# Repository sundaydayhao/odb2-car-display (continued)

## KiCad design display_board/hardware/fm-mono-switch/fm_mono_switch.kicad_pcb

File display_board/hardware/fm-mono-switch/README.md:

# RDA5807M + TS5A22364 单声道 FM / 环境传感小板 · A8

直接集成 **RDA5807M 裸芯片**、32.768 kHz 晶振、电源和天线接口。FM 与 ES8311（MP3 / 小智）经 TS5A22364 切换，共用 ESP32-P4 Function EV Board **v1.4** 的 NS4150B 功放和原喇叭。FM 左右声道经电阻合成单声道。

**状态：首板原型设计完成，已布线。KiCad 10.0.5 原生 ERC、DRC、原理图与 PCB 一致性均为零问题；106 个物理引脚的网络与设计意图一致。尚未做实物验证，不是量产验证版本。本次没有修改固件。**

A8新增 **DHT20 温湿度传感器（卧式、感应面朝上）** 和 **VEML7700-TT 光照传感器**，每套各1颗。板子加长至 **40×58mm**，原安装孔位置保留。新增J5两根线接开发板GPIO7/8；详细引脚、装配尺寸、外壳与固件接入见 [SENSORS.md](SENSORS.md)。

D1沿用A7的 **安世 PESD5V0F1BL,315 / C45961**。U3 **ME6211C30M5G-N**、Y1 **Y6OEL89CGI-STUYLC-32.768K** 和FM/音频部分的元件、焊盘、既有走线保持不变。

A6引入的音频方案继续使用 **TI TS5A22364DGSR / C105181，VSSOP-10 外露引脚**，0.5mm节距、3×3mm本体。TI标为ACTIVE；2026-09-24公开LCSC页面记录库存4719颗、1颗起购/步进，100颗报价阶梯USD0.4479/颗。库存未锁定，国内人民币价和即时交付以新配单为准。相较最早讨论的TS5A22362，本型号当次现货更多、价格更低；两者电气功能有差异，不能直接按同系列替换。A6重接U1的4/5/7/8脚，并将R5/R6改成1kΩ串联限流；必须使用A6或A7 PCB，不能在A5原板上直接换芯片。RDA5807M、GPIO及R83/R84外部接法不变。

## 文件

- `fm_mono_switch.kicad_pro`：打开工程；同名 `.kicad_sch` / `.kicad_pcb` 为完整原理图和已布线 PCB。
- `output/pdf/wiring.pdf`：三页中文接线和安装图，含 R83/R84 官方丝印位置及卧式传感器安装图。
- `output/pdf/schematic.pdf`：完整原理图，可放大查看。
- `output/board-3d.png`、`output/wiring.png`、`output/assembly.png`、`output/sensors.png`：预览；DHT20模型为简化机械包络。
- `PROCUREMENT.md`：逐项降本、原立创报价错配与交期说明。
- `BOM-LCSC-A8.csv`：只列每套用量，1套=1块小板；导入立创时把“每套用量”映射为数量，按实际需求填写采购套数。排针不装，损耗另加。
- `BOM-cost.csv`：每套用量、每套净用料参考金额、MOQ和来源。沿用已核对的阶梯单价，不代表购买1套时的成交价；重新配单确认。
- `BOM.csv`：分组工程物料表，明确列出“每套用量”；`output/fabrication/`：Gerber、钻孔和贴装坐标。
- `VERIFICATION.md`、`output/verification.json`：检查范围和文件校验值。
- `Mono.kicad_sym`、`Mono.pretty`、`libs/`：本地符号和历史库；U1为TI VSSOP-10，U2为MSOP-10，使用核对过的KiCad标准MSOP-10封装及模型。
- `reference/RDA5807M.pdf`：用户提供的裸芯片手册副本；其他依据见 `SOURCES.md`。

## 外部接线：4 根音频线 + 5 根电源 / 控制线 + 2 根传感器线

断电，**拆下开发板 R83、R84 两颗 0Ω 电阻**。保留 C39、C40、C58、C59、R146、R147。用万用表的导通档确认焊盘所属支路，再焊接细软线；不要按照片的左右方向猜测。

| 小板接口 | 开发板焊点 | 导通识别依据 |
|---|---|---|
| J1.1 / CP | R83 的 ES8311 侧焊盘 | 通向 C39 的 R83 侧焊盘 |
| J1.2 / CN | R84 的 ES8311 侧焊盘 | 通向 C40 的 R84 侧焊盘 |
| J2.1 / AP | R83 的功放侧焊盘 | 通向 C59 的 R83 侧焊盘 |
| J2.2 / AN | R84 的功放侧焊盘 | 通向 C58 的 R84 侧焊盘 |
| J4.1 / 3V3 | 开发板 J1.17 | 3.3 V 电源 |
| J4.2 / GND | 开发板 J1.20 | 共地 |
| J4.3 / SEL | 开发板 J1.15 | GPIO6，音源选择 |
| J4.4 / SDA | 开发板 J1.21 | GPIO2，FM I²C 数据 |
| J4.5 / SCL | 开发板 J1.19 | GPIO3，FM I²C 时钟 |
| J5.1 / SDA7 | 开发板 J1.3 | GPIO7，传感器 I²C 数据 |
| J5.2 / SCL8 | 开发板 J1.5 | GPIO8，传感器 I²C 时钟 |

小板 J1 是两针音频输入，**不是开发板的 J1 排针**。小板接口方形焊盘为 1 脚，J4 顶视图从标有 `3V3` 的方形焊盘依次为 `3V3 / G / SEL / SDA / SCL`。排针可不装，直接焊线。

小板 J3.1 `ANT` 接外置 FM 线天线，可先用约 70–80 cm 导线试验并根据安装环境调整；J3.2 `GND` 为地 / 同轴屏蔽连接。该输入没有车载有源天线的幻象供电。天线尽量远离屏幕排线、USB、DC/DC 和扬声器开关输出。

扬声器仍接开发板 **J16**。FM 接入的是功放之前的小信号通路；不要接到 J16 的 SPK+ / SPK−。四根音频飞线尽量短，CP/CN、AP/AN 分别成对布置，并固定线材以免拉脱焊盘。

## 工作原理与关键器件

| 部分 | 设计 |
|---|---|
| FM 接收 | U2 RDA5807M，MSOP-10，3.0 V 供电 |
| 时钟 | Y1 32.768 kHz 晶振接 RCLK 与 GND；按芯片参考电路使用内部振荡电路 |
| FM 电源 | U3 ME6211C30M5G-N；3.3 V → 3.0 V → FB1 → FM_VDD，C9/C10 就近去耦 |
| 射频输入 | J3 ANT → C6 100 pF → FMIN；D1 PESD5V0F1BL,315 低电容双向 ESD 管 |
| 合成单声道 | L/R 各串 1 µF 隔直及 10 kΩ，再汇合；不直接短接左右输出 |
| 音源切换 | U1 TS5A22364DGSR，两个 SPDT 同时切换功放正负两根输入 |
| 上电默认 | SEL 100 kΩ 下拉，GPIO6=0 接 ES8311，GPIO6=1 接 FM |
| 原功放 | 继续使用 NS4150B；小板上不增设功放 |

RDA5807M **裸芯片引脚**：1 GND、2 FMIN、3 GND、4 SCLK、5 SDIO、6 RCLK、7 VDD、8 GND、9 ROUT、10 LOUT。`fm-module` 目录中 RRD-102 成品模块的焊盘号不同，不能套用。截图出现的 `33.768 kHz` 是笔误，本板为 **32.768 kHz**。

TS5A22364 引脚：1 VCC；2 NO1=FM_MONO；3 COM1=AP；4 NC1=CODEC_P_SW；5 IN1=SEL；6 GND；7 IN2=SEL；8 NC2=CODEC_N_SW；9 COM2=AN；10 NO2=FM_REF。J1的CP/CN分别经R5/R6=1kΩ到NC1/NC2；FM_REF经R4=4.3kΩ接地。R7/R8=100kΩ为功放输入和被选中的音源提供直流参考。

TS5A22364由3.3V经R11=10Ω和C4/C5去耦供电。选通通路范围为VCC−5.5V至VCC，标称3.3V时约−2.2V至+3.3V；3.0V供电测试条件下Ron典型0.61Ω、全温最大0.97Ω，不能把典型值当作全条件保证。逻辑VIH≥1.4V、VIL≤0.6V，与GPIO兼容。未选通NC/NO会通过内部约25Ω放电，TI建议电流不超过±10mA；R5/R6改为1kΩ/1%，若输入瞬时绝对值≤3.6V，仅按最小990Ω计算电流≤3.64mA，FM通路由R1/R2各10kΩ限流。所有音源均经电容隔直，不能引入负直流。此限流计算不代替上电瞬态实测；软件继续停止未使用音源并执行功放静音切换。

I²C 经 R12/R13=100 Ω 串联，R14/R15=4.7 kΩ 拉到 FM_VDD（约 3.0 V）。ESP32 引脚使用开漏 I²C，关闭不需要的内部上拉；小板与主板一起供电。

## PCB 与装配

40 × 58 mm，双层，建议板厚 1.6 mm、1 oz 铜。两个 Ø2.2 mm 非金属化安装孔中心为板左上角起算 (3,3) 和 (37,33) mm，保留原固定点。板上阻容以 0603 为主，接口为 2.54 mm 排针。最小设计线宽 0.15 mm、间距 0.127 mm；普通过孔 0.6 / 0.3 mm。双面地平面已填充，DHT20本体下方两面禁止铺铜，以减小导热；信号细线允许通过。

- U4 DHT20按丝印轮廓**卧放、感应孔朝上**。四脚保持原顺序后弯折入孔，方焊盘为1脚VDD。外壳12.6×16.1×5.8mm，预留约0.5mm离板间隙，装配后本体顶面约6.3mm高；建议外壳局部留至少8mm净空再做首件核对。此高度不包括选装直插排针。
- DHT20在贴片工序后手焊，夹持引脚成形，不能在塑封根部硬折。不要用胶、泡棉或三防漆覆盖感应孔；外壳对应位置开通风孔。弯脚尺寸由首件实物确认。
- U5指定VEML7700-**TT顶视型**，不要换-TR侧视型。外壳开独立透光窗，避免显示屏漏光；装入最终外壳后校准透光衰减。温湿度区避免直晒与热源。

- **U1 TS5A22364DGSR 为 VSSOP-10 / DGS**，两侧外露引脚，3×3mm本体、0.5mm间距。使用已核对包络的KiCad标准MSOP-10焊盘（库命名不同，机械尺寸相容）；不买DRC/VSON或YZP/DSBGA封装。
- U2 是 MSOP-10、0.5 mm 间距；封装三角和模型圆点标明 1 脚。
- Y1 为扬兴 `Y6OEL89CGI-STUYLC-32.768K`（C19272781），目录参数 CL=12.5pF、ESR≤50kΩ、−40～85°C，DT-26 圆柱约 Ø2×6mm。引脚成形至1.9mm孔距。精确承认书与起振裕量仍需首板确认，不能用立创旧报价匹配的 SMD3215 晶体直接替换。
- D1 为安世 **PESD5V0F1BL,315**（C45961），双向、VRWM=5.5V，结电容典型0.4pF/最大0.55pF（1MHz、0V、25°C），SOD882 / DFN1006-2。推荐焊盘0.4×0.7mm、中心距0.7mm与现板一致；整机ESD效果未测试。
- U3 改用带 `-N` 的微盟3.0V稳压器；C7/C8 改4.7µF/10V/X5R，需核对偏压后的有效容量≥1µF并测启动、纹波；不要改用高压差 AMS1117。
- 工程 BOM 已补齐具体品牌、MPN 和商品编号。原用户报价单中的 RDA5807M 仍需订货7–10个工作日，100颗货源及封装须锁单前确认。候选 CPL/BOM 仍需贴片厂核对旋转和料号，不能直接视为下单审核完成。
- 接地 SMD 焊盘采用实连铺铜，装配时需充分预热。Y1、排针可在贴片后手工焊接。

## 软件模式切换

| 模式 | GPIO6 | 音频来源 |
|---|---|---|
| MP3 | 0 | ESP32 解码 → I²S → ES8311 |
| 小智 | 0 | ESP32 语音 → I²S → ES8311 |
| FM | 1 | RDA5807M → 无源合声 → 原功放 |

MP3 和小智共用 ES8311，二者的互斥由软件音频管理负责。进入 FM 时停止 / 静音 ES8311 播放；切换前静音或关闭原 PA，设置 GPIO6，待节点稳定再打开 PA 并淡入。原 PA 控制为 **GPIO53**，不需要增加飞线。FM 模式也需要软件使能这个功放。

现有 FM 驱动使用 GPIO2/3、100 kHz I²C、7 位顺序访问地址 0x10。固件应选择 32.768 kHz 参考时钟，按需要使用强制单声道和 FM 自身音量控制；切换静音延时以首板波形和听感调整。**硬件接线完成不等于现有固件已经实现 GPIO6 与 PA 的联动。**

## 首板检查

1. 焊接后先检查 U1/U2 引脚短路和芯片方向；未连接开发板音频焊盘时，单独检查电源与地是否短路。
2. 输入 3.3 V，确认 FM_VDD 约 3.0 V、U1 电源接近 3.3 V；确认 GPIO6 默认低电平。
3. 验证 I²C 通信、芯片初始化和搜台。普通高电容探头可能使手表晶振停振，优先由芯片工作状态判断或使用合适的低电容探头。
4. 接回 R83/R84 四根飞线，以低音量分别验证 MP3、小智、FM。确认 FM 模式仍打开原功放；测试切换有无明显爆音。
5. 在屏幕刷新、Wi-Fi 传输、USB 供电以及最终安装位置下验证底噪和 FM 接收，按需要调整天线与线束。

## 维护

脚本位于仓库 `tools/fm_mono_switch/`。A8使用交付的原生CAD文件维护；`generate.py`是历史A7生成器，已阻止覆盖A8。`add_sensors_a8.py`为一次性的A7到A8迁移，`route_sensors_a8.py`只为该迁移导入传感器布线。`route.py` / `finish_routes.py`是已拦截的历史A2流程。`finalize.py`整理料号，`verify_final.py`比对网表，`verify_a8_change.py`核对A7元件及全部既有走线保留，`draw_wiring_a2.py`生成当前三页接线图，`package_release.py`导出文件包。

只更新BOM时运行 `python tools/fm_mono_switch/export_bom.py`，不改写原理图和PCB。以后导出的工程表、采购表和成本表只列“每套用量”，不预乘采购套数。`procurement.json` 的 `price_reference_boards` 仅记录历史价格评估基准。

打开工程建议使用KiCad 10。U1/U2均用官方 `Package_SO:MSOP-10_3x3mm_P0.5mm`；U1符号和完整厂商手册已随工程提供。标准焊盘1.50×0.35mm、行中心距4.20mm，按厂商3×3mm本体、4.75–5.05mm引脚总宽复核；焊盘比推荐图的1.02×0.31mm更长，不冒称完全照搬推荐焊盘。

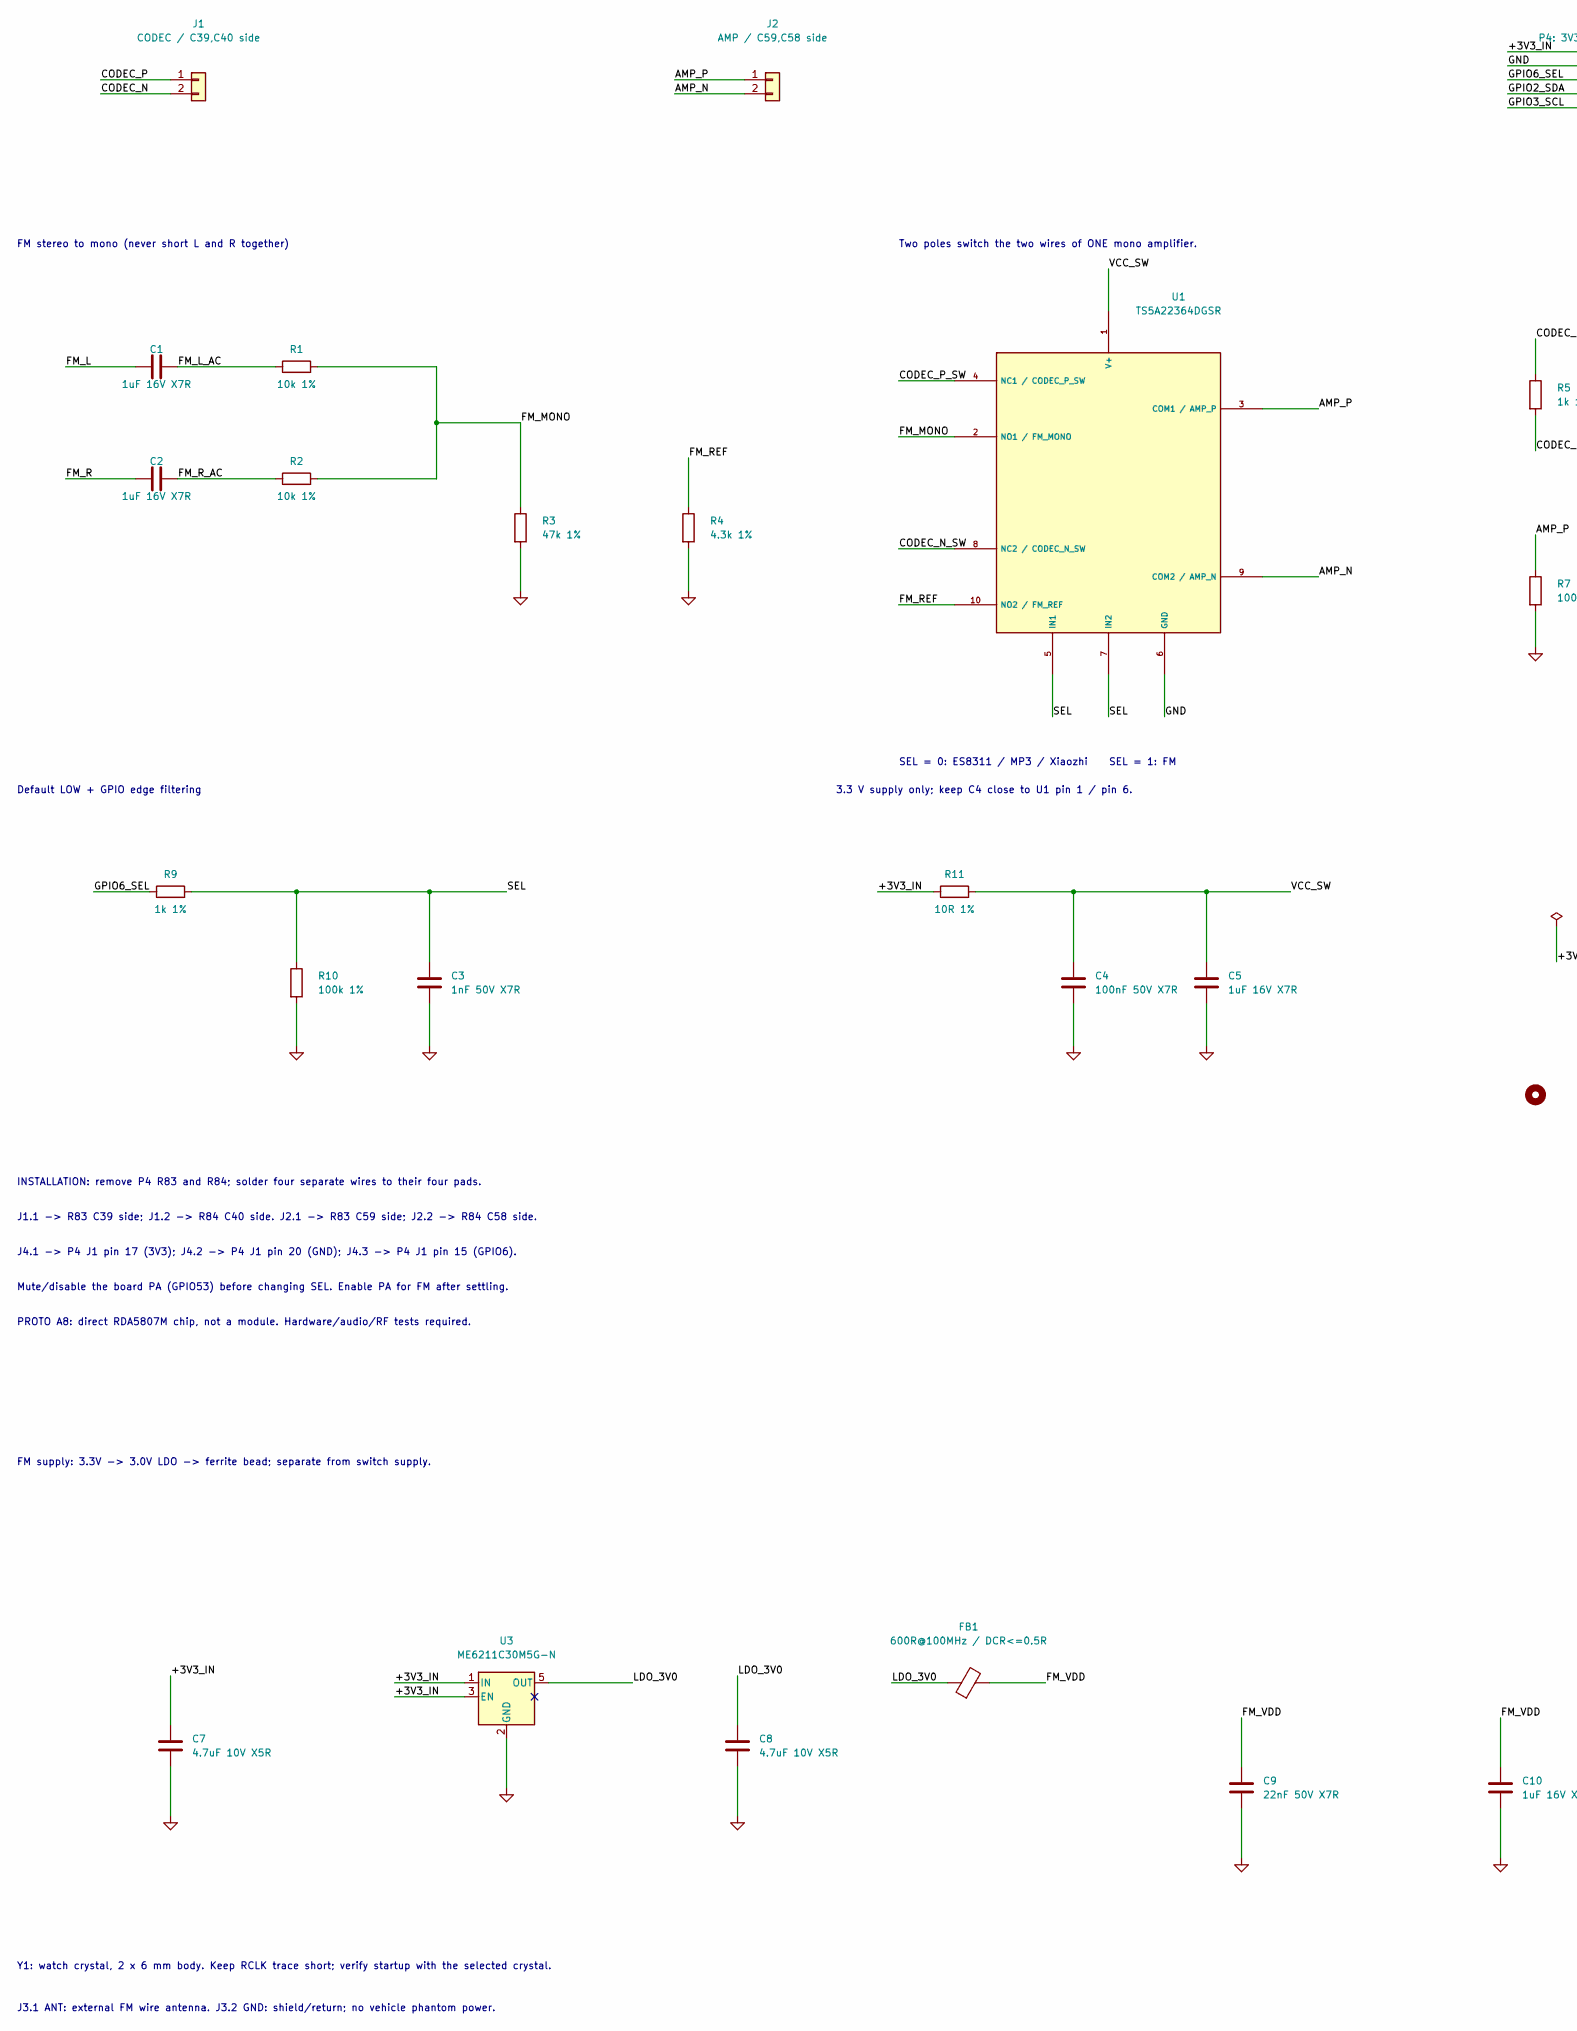
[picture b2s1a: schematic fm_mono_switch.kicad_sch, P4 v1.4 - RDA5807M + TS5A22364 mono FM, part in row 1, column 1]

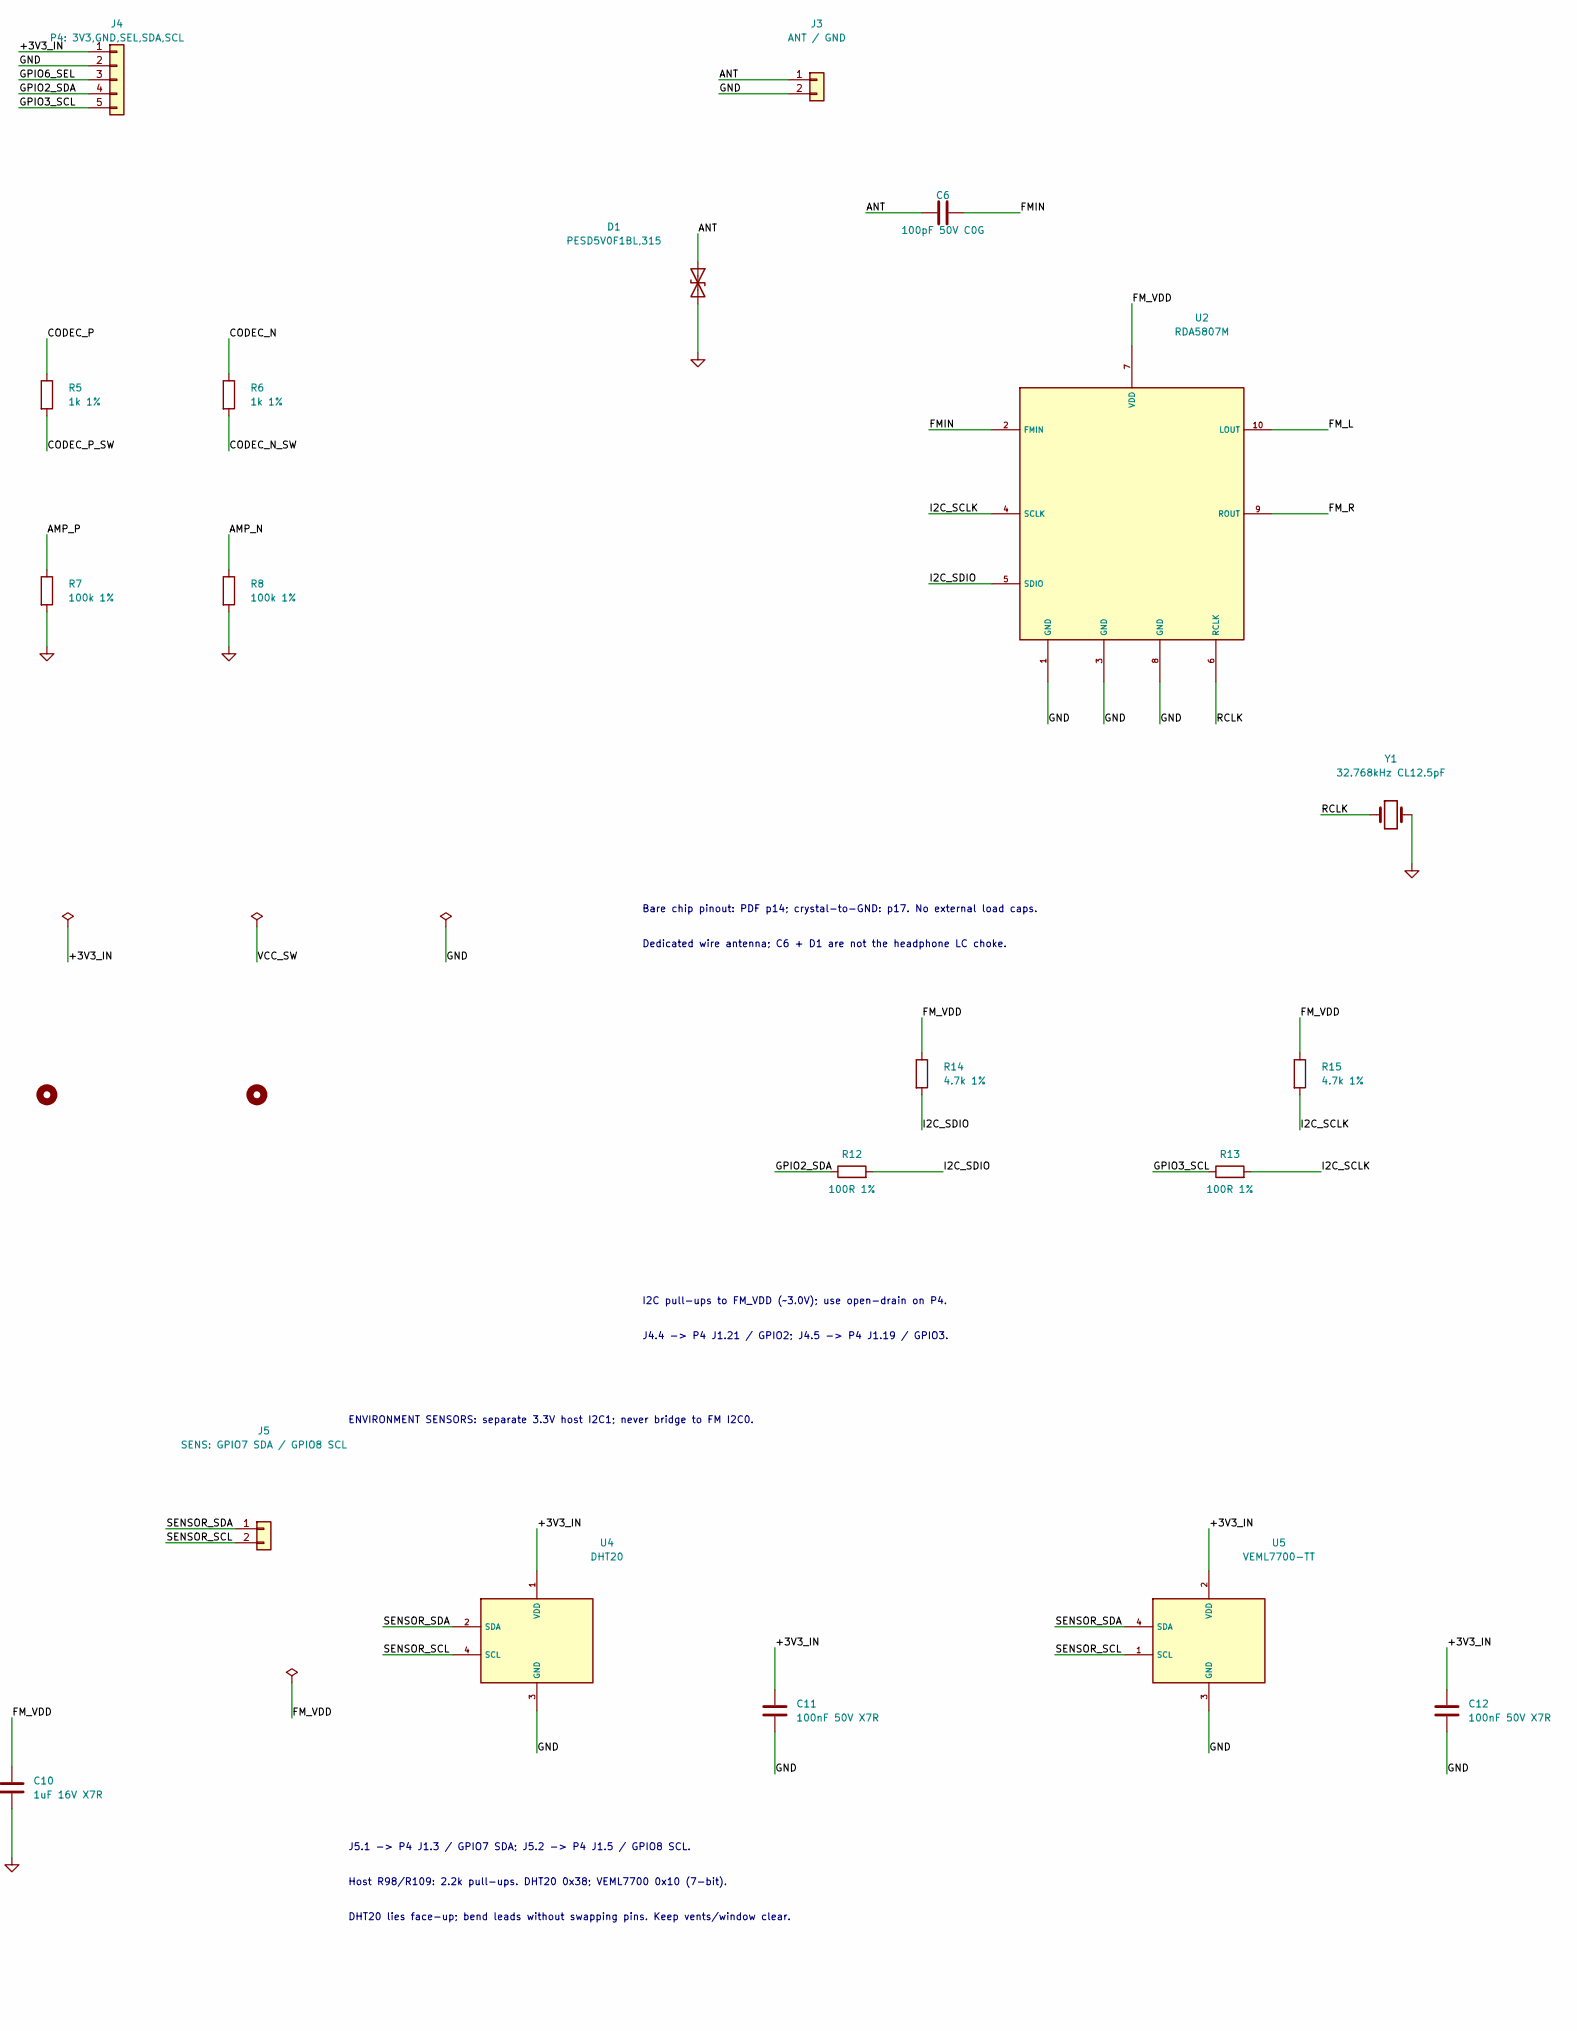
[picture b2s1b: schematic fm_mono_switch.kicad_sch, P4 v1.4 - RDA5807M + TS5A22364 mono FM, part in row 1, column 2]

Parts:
C1, C2, C5, C10: 1uF 16V X7R; C_0603_1608Metric; MPN 0603B105K160NT; LCSC C93816
C3: 1nF 50V X7R; C_0603_1608Metric; MPN 0603B102K500NT; LCSC C44369
C4, C11, C12: 100nF 50V X7R; C_0603_1608Metric; MPN 0603B104K500NT; LCSC C30926
C6: 100pF 50V C0G; C_0603_1608Metric; MPN 0603CG101J500NT; LCSC C1635
C7, C8: 4.7uF 10V X5R; C_0603_1608Metric; MPN 0603X475M100NT; LCSC C2857987
C9: 22nF 50V X7R; C_0603_1608Metric; MPN 0603B223K500NT; LCSC C77571
D1: PESD5V0F1BL,315; D_SOD-882; MPN PESD5V0F1BL,315; LCSC C45961
FB1: 600R@100MHz / DCR<=0.5R; R_0603_1608Metric; MPN CBG160808U601T; LCSC C73326
H1, H2: M2 NPTH; MountingHole_2.2mm_M2
J1: CODEC / C39,C40 side; PinHeader_1x02_P2.54mm_Vertical
J2: AMP / C59,C58 side; PinHeader_1x02_P2.54mm_Vertical
J3: ANT / GND; PinHeader_1x02_P2.54mm_Vertical
J4: P4: 3V3,GND,SEL,SDA,SCL; PinHeader_1x05_P2.54mm_Vertical
J5: SENS: GPIO7 SDA / GPIO8 SCL; PinHeader_1x02_P2.54mm_Vertical
R1, R2: 10k 1%; R_0603_1608Metric; MPN 0603WAF1002T5E; LCSC C25804
R3: 47k 1%; R_0603_1608Metric; MPN 0603WAF4702T5E; LCSC C25819
R4: 4.3k 1%; R_0603_1608Metric; MPN 0603WAF4301T5E; LCSC C23159
R5, R6, R9: 1k 1%; R_0603_1608Metric; MPN 0603WAF1001T5E; LCSC C21190
R7, R8, R10: 100k 1%; R_0603_1608Metric; MPN 0603WAF1003T5E; LCSC C25803
R11: 10R 1%; R_0603_1608Metric; MPN 0603WAF100JT5E; LCSC C22859
R12, R13: 100R 1%; R_0603_1608Metric; MPN 0603WAF1000T5E; LCSC C22775
R14, R15: 4.7k 1%; R_0603_1608Metric; MPN 0603WAF4701T5E; LCSC C23162
U1: TS5A22364DGSR; MSOP-10_3x3mm_P0.5mm; MPN TS5A22364DGSR; LCSC C105181
U2: RDA5807M; MSOP-10_3x3mm_P0.5mm; MPN RDA5807M; LCSC C82537
U3: ME6211C30M5G-N; SOT-23-5; MPN ME6211C30M5G-N; LCSC C403651
U4: DHT20; DHT20_Horizontal; MPN DHT20; LCSC C3012627
U5: VEML7700-TT; VEML7700_TT; MPN VEML7700-TT; LCSC C1850416
Y1: 32.768kHz CL12.5pF; Crystal_C26-LF_D2.1mm_L6.5mm_Horizontal; MPN Y6OEL89CGI-STUYLC-32.768K; LCSC C19272781

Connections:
/+3V3_IN: C7.1, C11.1, C12.1, J4.1, R11.1, U3.1 (IN), U3.3 (EN), U4.1 (VDD), U5.2 (VDD)
/AMP_N: J2.2, R8.1, U1.9 (COM2 / AMP_N)
/AMP_P: J2.1, R7.1, U1.3 (COM1 / AMP_P)
/ANT: C6.1, D1.1 (A1), J3.1
/CODEC_N: J1.2, R6.1
/CODEC_N_SW: R6.2, U1.8 (NC2 / CODEC_N_SW)
/CODEC_P: J1.1, R5.1
/CODEC_P_SW: R5.2, U1.4 (NC1 / CODEC_P_SW)
/FMIN: C6.2, U2.2 (FMIN)
/FM_L: C1.1, U2.10 (LOUT)
/FM_L_AC: C1.2, R1.1
/FM_MONO: R1.2, R2.2, R3.1, U1.2 (NO1 / FM_MONO)
/FM_R: C2.1, U2.9 (ROUT)
/FM_REF: R4.1, U1.10 (NO2 / FM_REF)
/FM_R_AC: C2.2, R2.1
/FM_VDD: C9.1, C10.1, FB1.2, R14.1, R15.1, U2.7 (VDD)
/GPIO2_SDA: J4.4, R12.1
/GPIO3_SCL: J4.5, R13.1
/GPIO6_SEL: J4.3, R9.1
/I2C_SCLK: R13.2, R15.2, U2.4 (SCLK)
/I2C_SDIO: R12.2, R14.2, U2.5 (SDIO)
/LDO_3V0: C8.1, FB1.1, U3.5 (OUT)
/RCLK: U2.6 (RCLK), Y1.1
/SEL: C3.1, R9.2, R10.1, U1.5 (IN1), U1.7 (IN2)
/SENSOR_SCL: J5.2, U4.4 (SCL), U5.1 (SCL)
/SENSOR_SDA: J5.1, U4.2 (SDA), U5.4 (SDA)
/VCC_SW: C4.1, C5.1, R11.2, U1.1 (V+)
GND: C3.2, C4.2, C5.2, C7.2, C8.2, C9.2, C10.2, C11.2, C12.2, D1.2 (A2), J3.2, J4.2, R3.2, R4.2, R7.2, R8.2, R10.2, U1.6 (GND), U2.1 (GND), U2.3 (GND), U2.8 (GND), U3.2 (GND), U4.3 (GND), U5.3 (GND), Y1.2

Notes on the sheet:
FM stereo to mono (never short L and R together)
Two poles switch the two wires of ONE mono amplifier.
SEL = 0: ES8311 / MP3 / Xiaozhi SEL = 1: FM
Default LOW + GPIO edge filtering
3.3 V supply only; keep C4 close to U1 pin 1 / pin 6.
INSTALLATION: remove P4 R83 and R84; solder four separate wires to their four pads.
J1.1 -> R83 C39 side; J1.2 -> R84 C40 side. J2.1 -> R83 C59 side; J2.2 -> R84 C58 side.
J4.1 -> P4 J1 pin 17 (3V3); J4.2 -> P4 J1 pin 20 (GND); J4.3 -> P4 J1 pin 15 (GPIO6).
Mute/disable the board PA (GPIO53) before changing SEL. Enable PA for FM after settling.
PROTO A8: direct RDA5807M chip, not a module. Hardware/audio/RF tests required.
Bare chip pinout: PDF p14; crystal-to-GND: p17. No external load caps.
Dedicated wire antenna; C6 + D1 are not the headphone LC choke.
I2C pull-ups to FM_VDD (~3.0V); use open-drain on P4.
J4.4 -> P4 J1.21 / GPIO2; J4.5 -> P4 J1.19 / GPIO3.
FM supply: 3.3V -> 3.0V LDO -> ferrite bead; separate from switch supply.
Y1: watch crystal, 2 x 6 mm body. Keep RCLK trace short; verify startup with the selected crystal.
J3.1 ANT: external FM wire antenna. J3.2 GND: shield/return; no vehicle phantom power.
ENVIRONMENT SENSORS: separate 3.3V host I2C1; never bridge to FM I2C0.
J5.1 -> P4 J1.3 / GPIO7 SDA; J5.2 -> P4 J1.5 / GPIO8 SCL.
Host R98/R109: 2.2k pull-ups. DHT20 0x38; VEML7700 0x10 (7-bit).
DHT20 lies face-up; bend leads without swapping pins. Keep vents/window clear.

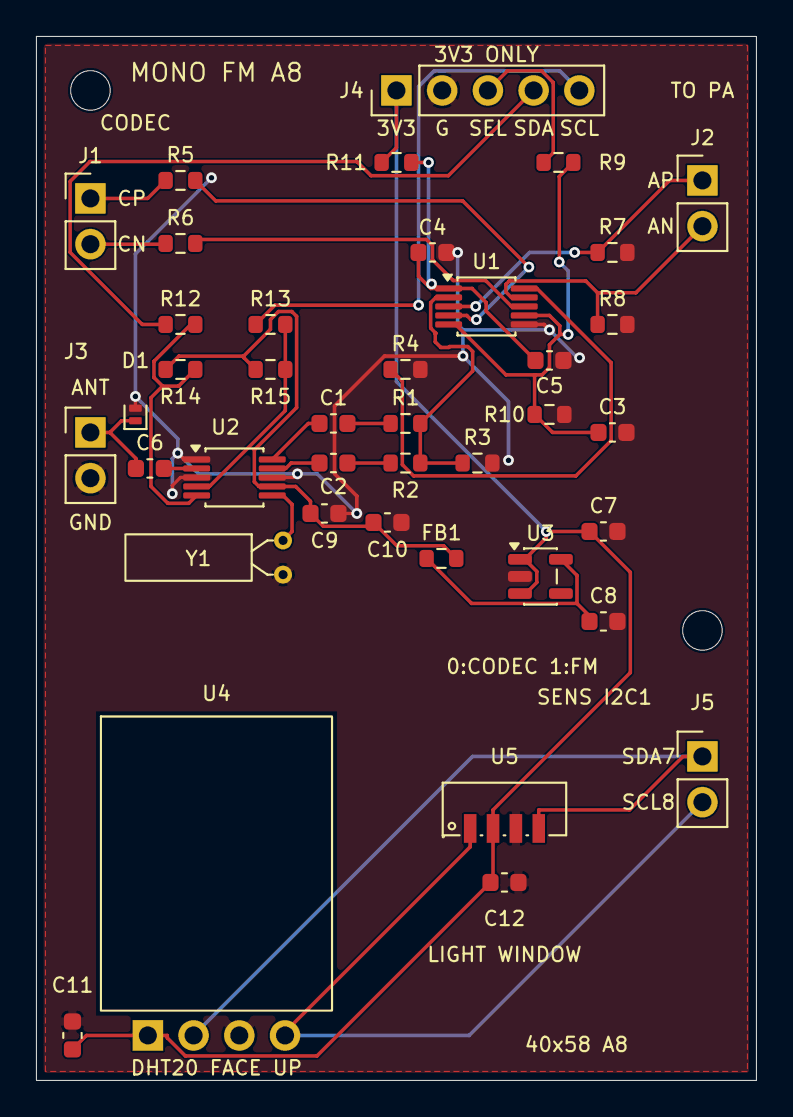
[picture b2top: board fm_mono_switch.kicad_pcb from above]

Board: 2 copper layers, 40.0 x 58.0 mm, 42 parts (0 on the bottom side), 28 nets.

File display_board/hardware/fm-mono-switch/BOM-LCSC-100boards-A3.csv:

商品编号,型号,品牌,封装,数量,位号,备注
C700220,SGM3718YUWQ10G/TR,SG Micro / 圣邦微,UTQFN-10L(1.4x1.8),100,U1,保留；需要支持隔直后负向音频，普通 4053 不能直接替换。UTQFN 回流焊。
C82537,RDA5807M,RDA / 锐迪科,MSOP-10,100,U2,保留 MSOP-10 裸芯片。用户2026-09-24立创报价：MOQ5、库存0、订货预估7–10工作日，5颗档¥1.0483；100颗报价/交期和封装待锁单确认。C82537为原目录编号，不能直接套用于无商品编号的订货渠道。不得用SOP-8直接替代。
C403651,ME6211C30M5G-N,Microne / 南京微盟,SOT-23-5,100,U3,替换 TLV75530PDBVR；3.0V、SOT-23-5、1 VIN/2 GND/3 CE/4 NC/5 VOUT。选带 -N 新版，保持 CE 接输入。低压差与噪声需首板验证。
C172421,LESD8LL5.0CT5G,LRC / 乐山无线电,SOD-882,100,D1,替换 Nexperia PESD5V0F1BL；双向、5V、0.25pF 典型/0.3pF 最大、SOD-882。钳位性能不宣称等同，整机 ESD 待测。
C19272781,Y6OEL89CGI-STUYLC-32.768K,YXC / 扬兴,DT-26,100,Y1,替换 Abracon；目录规格 32.768kHz、CL12.5pF、ESR50kΩ、±10ppm、-40~85°C、DT-26 2×6mm。引脚成形到 1.9mm；电气参数按目录核对，精确承认书与起振裕量待首板确认。不要换成 -20~70°C 版本。
C73326,CBG160808U601T,FH / 风华高科,0603,100,FB1,保留滤波功能并指定常备国产料；0603、200mA、DCR≤0.5Ω，20mA 时压降≤10mV。
C93816,0603B105K160NT,FH / 风华高科,0603,400,"C1,C2,C5,C10",1µF/16V/X7R/±10%/0603；合并同规格采购，保留音频耦合容量和电源去耦。
C44369,0603B102K500NT,FH / 风华高科,0603,100,C3,控制脚 RC 滤波改 X7R；不是射频或音频耦合电容，无需 C0G 精度。
C30926,0603B104K500NT,FH / 风华高科,0603,100,C4,100nF/50V/X7R/±10%/0603；选常见库存规格，50V 是此料号耐压，不是板上供电要求。
C1635,0603CG101J500NT,FH / 风华高科,0603,100,C6,射频耦合保留 C0G、±5%，不能跟 C3 一起改为 X7R/Y5V。
C2857987,0603X475M100NT,FH / 风华高科,0603,200,"C7,C8",由 4.7µF/16V/X7R 改常见 4.7µF/10V/X5R/±20%，工作约 3.3/3.0V。必须保证偏压温度下有效容量≥1µF；未取得本料号偏压曲线，首板测启动/纹波/负载响应。X5R 上限85°C。
C77571,0603B223K500NT,FH / 风华高科,0603,100,C9,22nF/50V/X7R/±10%/0603；保留参考设计近端去耦。
C25804,0603WAF1002T5E,UNI-ROYAL / 厚声,0603,200,"R1,R2",10kΩ、1%、0.1W、0603；保留左右声道隔离与求和，不能短接。
C25819,0603WAF4702T5E,UNI-ROYAL / 厚声,0603,100,R3,47kΩ、1%、0.1W、0603；保留音频直流参考。
C23159,0603WAF4301T5E,UNI-ROYAL / 厚声,0603,100,R4,4.3kΩ、1%、0.1W、0603；保留 FM 参考支路近似阻抗匹配。
C25803,0603WAF1003T5E,UNI-ROYAL / 厚声,0603,500,"R5,R6,R7,R8,R10",100kΩ、1%、0.1W、0603；合并采购，保留音频参考与上电默认状态。
C21190,0603WAF1001T5E,UNI-ROYAL / 厚声,0603,100,R9,1kΩ、1%、0.1W、0603；GPIO 串联滤波。
C22859,0603WAF100JT5E,UNI-ROYAL / 厚声,0603,100,R11,10Ω、1%、0.1W、0603；保留开关电源 RC 去耦。
C22775,0603WAF1000T5E,UNI-ROYAL / 厚声,0603,200,"R12,R13",100Ω、1%、0.1W、0603；I²C 飞线阻尼，不建议省掉。
C23162,0603WAF4701T5E,UNI-ROYAL / 厚声,0603,200,"R14,R15",4.7kΩ、1%、0.1W、0603；上拉到 FM_VDD，保留。

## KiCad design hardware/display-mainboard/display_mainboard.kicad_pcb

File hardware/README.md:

# 硬件工程

- [display-singleboard](display-singleboard/README.md)：当前 7 寸显示端主方案，P4 + C6、LCD 电源 / 背光 / 触摸集成，120 × 74 mm、4 层。
- [obd-ble-node](obd-ble-node/)：独立 OBD 蓝牙采集节点。
- [display-mainboard](display-mainboard/README.md) / [display-lcd-adapter](display-lcd-adapter/README.md)：合板前的参考检查点，不是当前显示端制作方案。

显示屏自带的 LCD 和触摸排线直接连接单板。前期实机验证使用官方 ESP32-P4 验证板；自研板的 CAD 检查结果及实物验证边界见各工程说明。

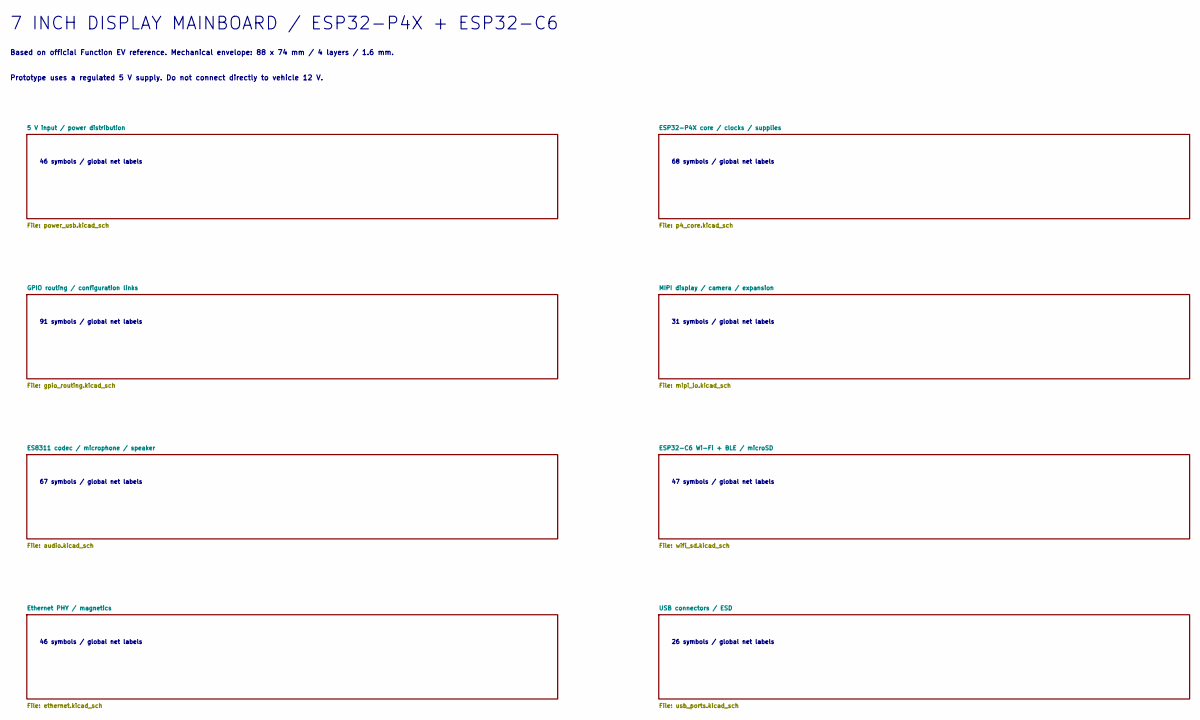
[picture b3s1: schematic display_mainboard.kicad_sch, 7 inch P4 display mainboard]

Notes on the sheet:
7 INCH DISPLAY MAINBOARD / ESP32-P4X + ESP32-C6
Based on official Function EV reference. Mechanical envelope: 88 x 74 mm / 4 layers / 1.6 mm.
Prototype uses a regulated 5 V supply. Do not connect directly to vehicle 12 V.
46 symbols / global net labels
68 symbols / global net labels
91 symbols / global net labels
31 symbols / global net labels
67 symbols / global net labels
47 symbols / global net labels
26 symbols / global net labels
